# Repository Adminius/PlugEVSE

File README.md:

# PlugEVSE
Mit PlugEVSE kann man ein Elektroauto aufladen. 
Vorteil ist, dass die komplette Elektronik (außer Fehlerstromschutzschalter) direkt im Type 2 Stecker verbaut ist.
PlugEVSE basiert auf dem Schaltplan von AnalogEVSE: http://www.analogevse.xyz/ 
Viele Informationen, z.B. Funktionsweise und Troubleshooting können der Seite entnommen werden.
Die größte Änderung im Vergleich zu AnalogEVSE ist die Umstellung auf SMD Bauteile um Platz zu sparen. Zusätzlich wurden Relais und Netzteil "ausgelagert".

## Was kann PlugEVSE:
- Laden mit fest eingestellter Stromstärke, z.B. mit 16A oder 32A (andere Werte sind möglich)

## Was kann PlugEVSE nicht:
- Erdungsüberwachung. Deswegen ist empfohlen PlugEVSE nur an geprüftem Anschluss mit funktionierender Erdung zu nutzen
- Es wird eine Fehlerstromschutzschalter Typ A EV oder Typ B vorausgesetzt. 

# ACHTUNG
- Wenn Begrife "Erdung" oder "Fehlerstromschutzschalter" nicht bekannt sind, dann ist dieses Projekt nichts für Sie! Sorry!
- Beim Zusammenbau wird mit **lebensgefährlicher** Netzspannung gearbeitet!
- Die Nutzung erfolgt auf eigene Gefahr. Ich übernehme keine Haftung!

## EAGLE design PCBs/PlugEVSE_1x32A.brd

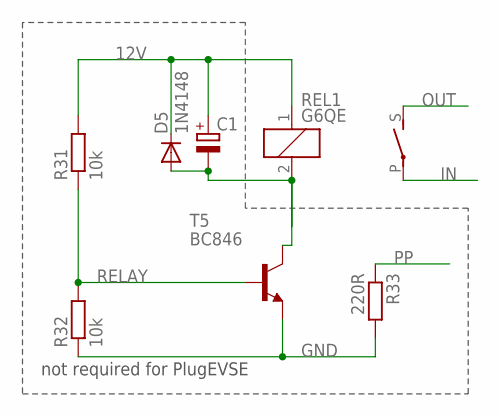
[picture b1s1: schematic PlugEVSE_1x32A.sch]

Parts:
C1: CPOL-EUSMCC; SMC_C
D5: 1N4148; SOD123
R31, R32: 10k; R0603
R33: 220R; R2512
REL1: G6QE
T5: BC846; SOT23

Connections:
12V: C1.+, D5.C, R31.2, REL1.1
GND: R32.1, R33.2, T5.2 (E)
IN: REL1.P
OUT: REL1.S
PP: R33.1
RELAY: R31.1, R32.2, T5.1 (B)
RL: C1.-, D5.A, REL1.2, T5.3 (C)

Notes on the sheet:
not required for PlugEVSE

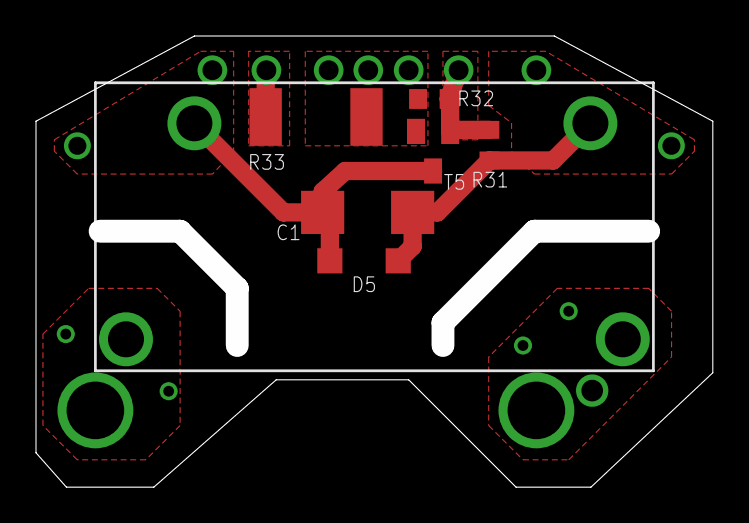
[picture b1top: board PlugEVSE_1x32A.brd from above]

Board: 2 copper layers, 36.3 x 23.8 mm, 7 parts (0 on the bottom side), 4 nets.

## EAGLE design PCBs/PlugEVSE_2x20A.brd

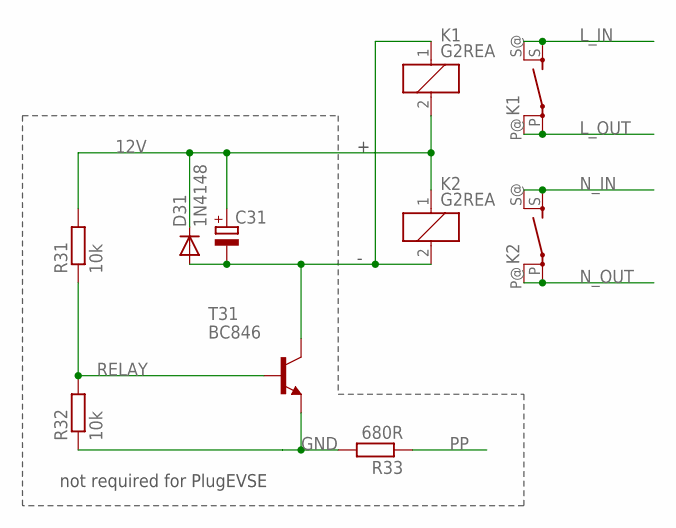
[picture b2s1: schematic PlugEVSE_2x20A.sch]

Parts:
C31: CPOL-EUSMCC; SMC_C
D31: 1N4148; SOD123
K1, K2: G2REA
R31, R32: 10k; R0603
R33: 680R; R2512
T31: BC846; SOT23

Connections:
12V: C31.+, D31.C, K1.2, K2.1, R31.2
GND: R32.1, R33.2, T31.2 (E)
L_IN: K1.S, K1.S@ (S)
L_OUT: K1.P, K1.P@
N_IN: K2.S, K2.S@ (S)
N_OUT: K2.P, K2.P@
PP: R33.1
RELAY: R31.1, R32.2, T31.1 (B)
RL: C31.-, D31.A, K1.1, K2.2, T31.3 (C)

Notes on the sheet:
not required for PlugEVSE

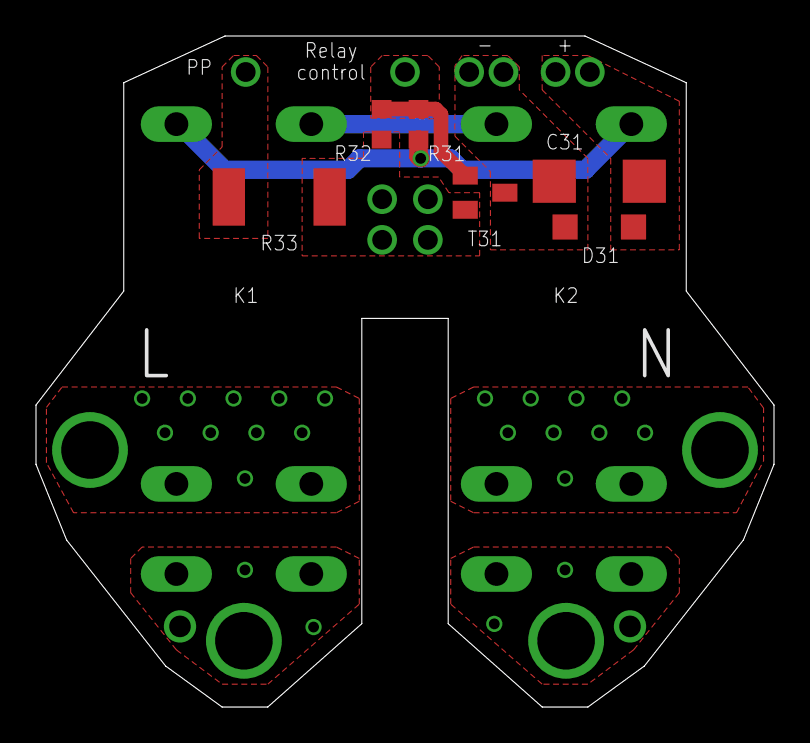
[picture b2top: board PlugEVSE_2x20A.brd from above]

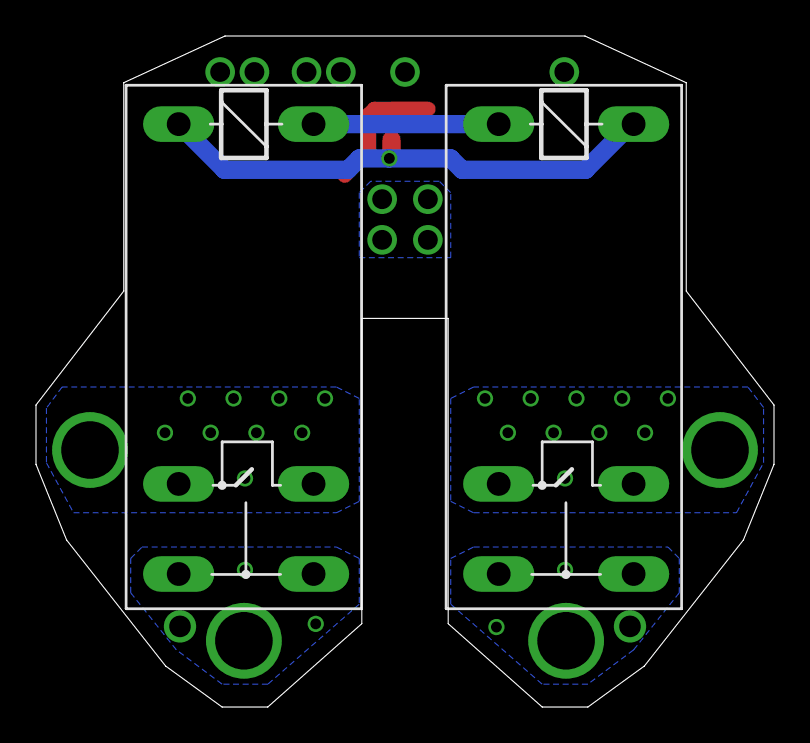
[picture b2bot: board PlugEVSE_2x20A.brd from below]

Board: 2 copper layers, 41.0 x 37.3 mm, 8 parts (2 on the bottom side), 8 nets.

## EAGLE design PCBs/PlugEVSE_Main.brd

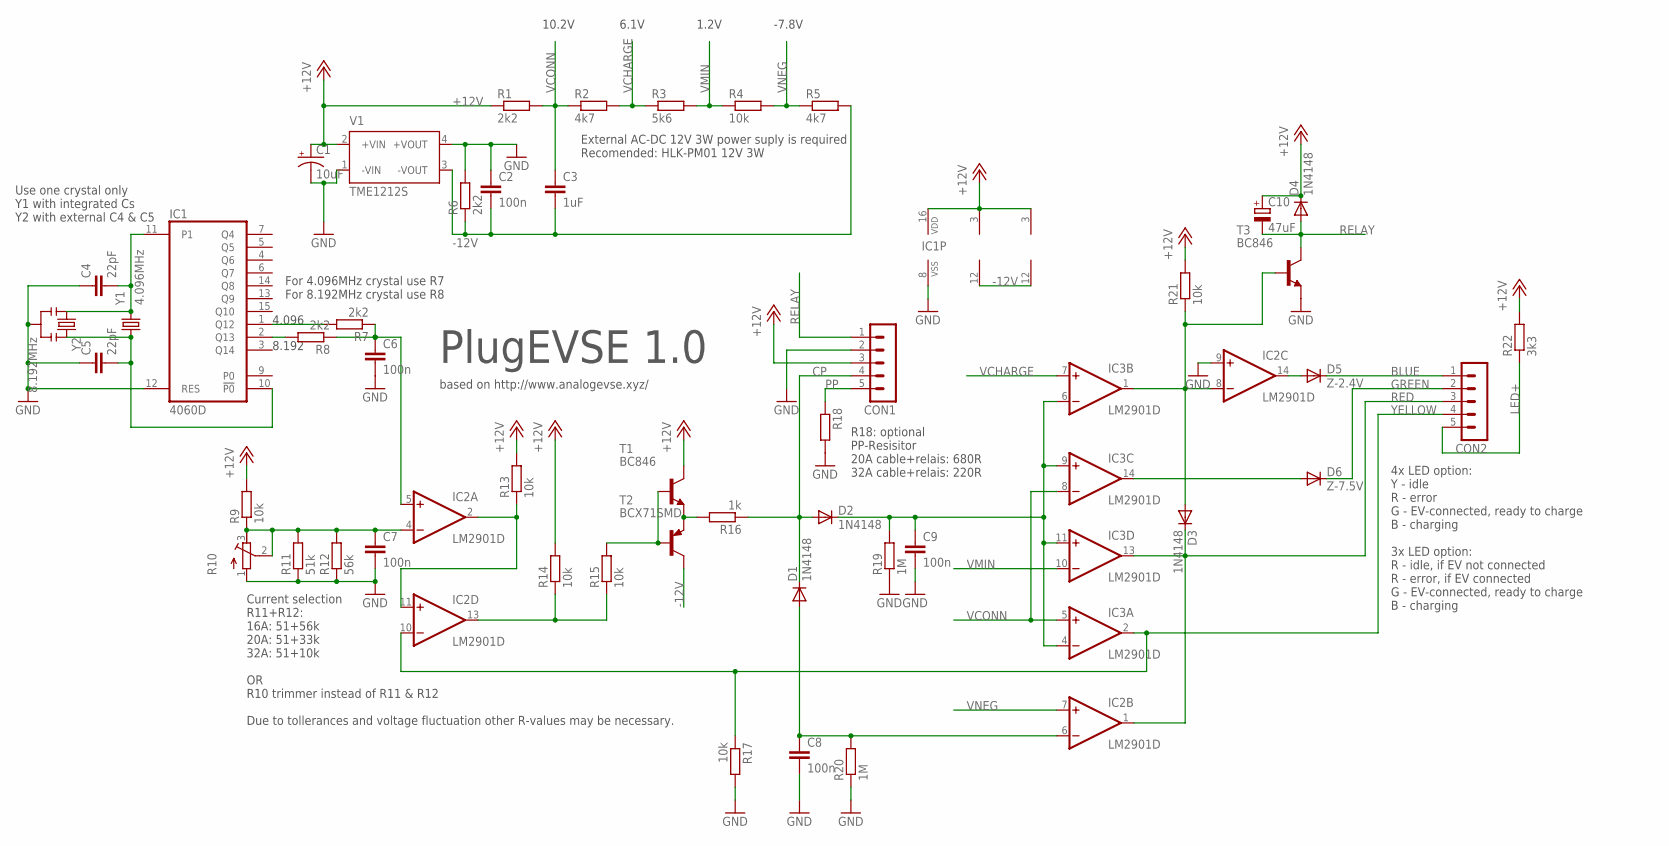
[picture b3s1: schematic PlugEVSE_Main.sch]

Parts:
C1: 10uF; EIA3216
C2, C6, C7, C8, C9: 100n; C0603
C3: 1uF; C0603
C4, C5: 22pF; C0603
C10: 47uF; E2,5-5
CON1, CON2: MA05-1
D1, D2, D3, D4: 1N4148; SOD123
D5: Z-2.4V; SOD123
D6: Z-7.5V; SOD123
IC1: 4060D; SO16
IC2, IC3: LM2901D; SO14
R1, R6, R7, R8: 2k2; R0603
R2, R5: 4k7; R0603
R3: 5k6; R0603
R4, R9, R13, R14, R15, R17, R21: 10k; R0603
R10: R-TRIMM3202; RTRIM3202
R11: 51k; R0603
R12: 56k; R0603
R16: 1k; R0603
R18: R-EU_R2512; R2512
R19, R20: 1M; R0603
R22: 3k3; R0603
T1, T3: BC846; SOT23
T2: BCX71SMD; SOT23
V1: TME1212S; TME
Y1: 4.096MHz; 11.4X4.5
Y2: 8.192MHz; RESONATOR-SMD

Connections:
+12V: C1.A (+), C10.+, CON1.3, D4.C, IC1.16 (VDD), IC2.3 (V+), IC3.3 (V+), R1.1, R9.2, R13.2, R14.2, R21.2, R22.2, T1.3 (C), V1.2 (+VIN)
-12V: C2.2, C3.2, IC2.12 (V-), IC3.12 (V-), R5.2, R6.1, T2.3 (C), V1.3 (-VOUT)
BLUE: CON2.1, D5.C
CP: CON1.4, D1.C, D2.A, R16.1
GND: C1.C (-), C2.1, C4.1, C5.1, C6.2, C7.2, C8.2, C9.2, CON1.2, IC1.8 (VSS), IC1.12 (RES), IC2.9 (+IN), R6.2, R10.1 (A), R11.1, R12.1, R17.2, R18.2, R19.1, R20.1, T3.2 (E), V1.1 (-VIN), V1.4 (+VOUT), Y2.2
GREEN: CON2.2, D6.C
LED+: CON2.5, R22.1
unnamed: R16.2, T1.2 (E), T2.2 (E)
unnamed: IC1.2 (Q13), R8.2
unnamed: IC1.1 (Q12), R7.2
unnamed: C6.1, IC2.5 (+IN), R7.1, R8.1
unnamed: IC2.13 (OUT), R14.1, R15.1
unnamed: C8.1, D1.A, IC2.6 (-IN), R20.2
unnamed: C9.1, D2.C, IC3.4 (-IN), IC3.6 (-IN), IC3.9 (+IN), IC3.11 (+IN), R19.2
unnamed: D3.A, IC2.8 (-IN), IC3.1 (OUT), R21.1, T3.1 (B)
unnamed: C7.1, IC2.4 (-IN), R9.1, R10.2 (S), R10.3 (E), R11.2, R12.2
unnamed: IC2.2 (OUT), IC2.11 (+IN), R13.1
unnamed: R15.2, T1.1 (B), T2.1 (B)
unnamed: C4.2, IC1.11 (P1), Y1.2, Y2.1
unnamed: D5.A, IC2.14 (OUT)
unnamed: D6.A, IC3.14 (OUT)
unnamed: C5.2, IC1.10 (!P0), Y1.1, Y2.3
PP: CON1.5, R18.1
RED: CON2.3, D3.C, IC2.1 (OUT), IC3.13 (OUT)
RELAY: C10.-, CON1.1, D4.A, T3.3 (C)
VCHARGE: IC3.7 (+IN), R2.2, R3.1
VCONN: C3.1, IC3.5 (+IN), IC3.8 (-IN), R1.2, R2.1
VMIN: IC3.10 (-IN), R3.2, R4.1
VNEG: IC2.7 (+IN), R4.2, R5.1
YELLOW: CON2.4, IC2.10 (-IN), IC3.2 (OUT), R17.1

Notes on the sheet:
10.2V
6.1V
1.2V
-7.8V
8.192
4.096
Current selection R11+R12: 16A: 51+56k 20A: 51+33k 32A: 51+10k OR R10 trimmer instead of R11 & R12 Due to tollerances and voltage fluctuation other R-values may be necessary.
Use one crystal only Y1 with integrated Cs Y2 with external C4 & C5
For 4.096MHz crystal use R7 For 8.192MHz crystal use R8
4x LED option: Y - idle R - error G - EV-connected, ready to charge B - charging 3x LED option: R - idle, if EV not connected R - error, if EV connected G - EV-connected, ready to charge B - charging
PlugEVSE 1.0
based on http://www.analogevse.xyz/
R18: optional PP-Resisitor 20A cable+relais: 680R 32A cable+relais: 220R
External AC-DC 12V 3W power suply is required Recomended: HLK-PM01 12V 3W

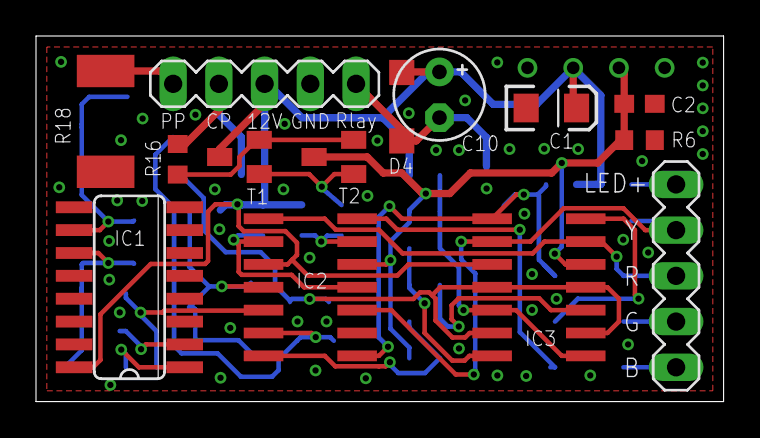
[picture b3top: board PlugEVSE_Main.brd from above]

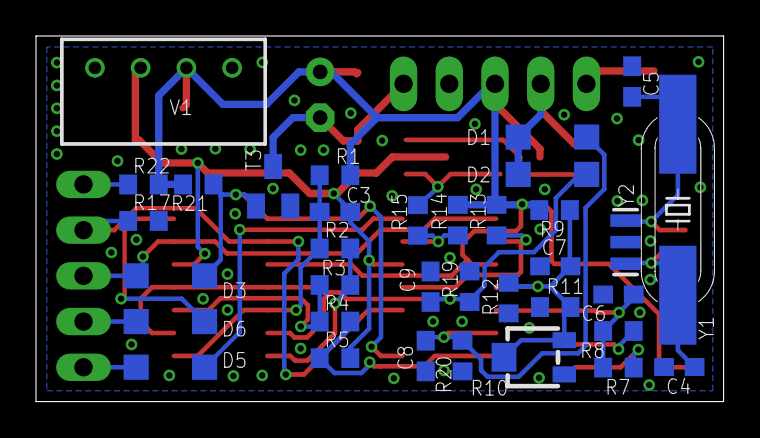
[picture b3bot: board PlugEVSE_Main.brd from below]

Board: 2 copper layers, 38.2 x 20.3 mm, 49 parts (35 on the bottom side), 30 nets.

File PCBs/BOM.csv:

Part;Desc;Long Desc;Case;Manuf. Partnr.;Mouser;Comment
D1;Z-Diode;2.4V;SOD-123;MMSZ4681-E3-08;78-MMSZ4681-E3-08;
D2;Z-Diode;7.5V;SOD-123;MMSZ5236B-E3-08;78-MMSZ5236B-E3-08;
D3,D4,D5,D6;Diode;1N4148;SOD-123;1N4148W-7-F;621-1N4148W-F;
V1;DC-DC;Isol. DC-DC 12V;;CRE1S1212SC;580-CRE1S1212SC;
IC2,IC3;IC;LM2901;SOIC-14 D;LM2901DRG3;595-LM2901DRG3;
IC1;IC;CD4060B;SO-16;CD4060BNSR;595-CD4060BNSR;
Y2;8.192 MHz;8.192 MHz Resonator;;CSTNE8M19G550000R0;81-CSTNE8M19G550000R;Alt: Y1+C4,C5
Y1;4.096 MHz;4.096 MHz Resonator;;ABLS-4.096MHz-D-3-Y-T;815-ABLS4096MHZD3YT;
;;;;;;
T1,T3;NPN;NPN Transistor;SOT23;BC817K-40HR;771-BC817K-40HR;
T2;PNP;PNP Transistor;SOT23;BC857B,215;771-BC857B-T/R;
;;;;;;
R10;Trimm-R;;3mm;TC33X-1-473E;652-TC33X-1-473E;current selection
R1,R6,R7,R8;2K2 0603;;0603;;;
R22;3K3 0603;;0603;;;
R2,R5;4K7 0603;;0603;;;
R3;5K6 0603;;0603;;;
R16;1K 0603;;0603;;;
R4,R9,R13,R14,R15,R17,R21;10K 0603;;0603;;;
R19,R20;1M 0603;;0603;;;
R11,R12;51K 0603;;0603;;;current selection
R11,R12;56K 0603;;0603;;;current selection
R12;33K 0603;;0603;;;current selection
R18;220/680R;220/680R 1W 2512;2512;;;optional, PP-resistor
C1;10uF;10uF 3216 Tantalum;3216;;;
C2,C6,C7,C8,C9;100n;;0603;;;
C3;1uF;;0603;;;
C4,C5;22pF;;0603;;;only for Y1
C10;47uF;47uF Radial Cap.;5mm;860010372004;710-860010372004;
;;;;;;
LED;RGB LED;RGB LED;5mm;HV-5RGB60;743-HV-5RGB60;
;;;;;;
Relais 23A;23A Relais;;;G2RL-1A-E2-CV-HA DC12;653-G2RL1AE2CVHADC12;
Relais 36A;36A Relais;;;G6QE-1A DC12;653-G6QE-1ADC12;
;;;;;;
Type 2 Plug;;;;DUOSIDA;;20A or 32A version, single phase

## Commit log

2020-06-29 intital commit

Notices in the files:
parts and their libraries:
crystal-geyer_V1_0: Copyright: Geyer-Electronic
